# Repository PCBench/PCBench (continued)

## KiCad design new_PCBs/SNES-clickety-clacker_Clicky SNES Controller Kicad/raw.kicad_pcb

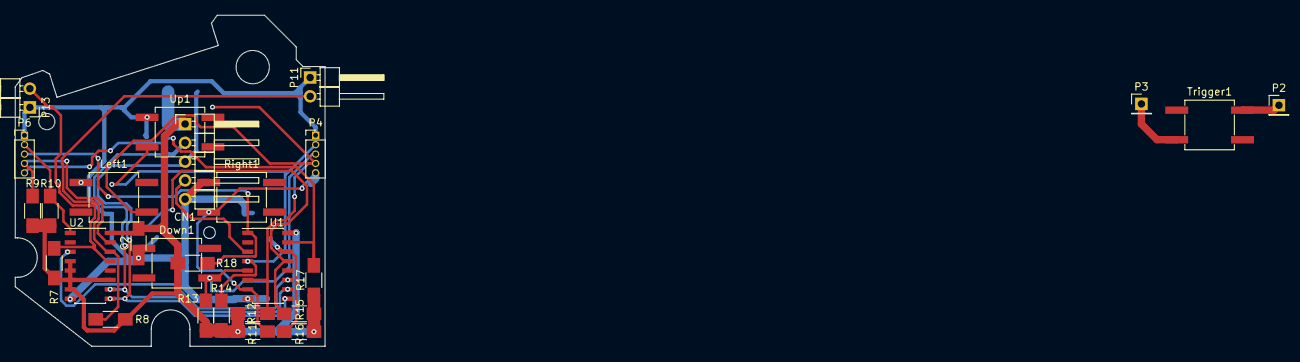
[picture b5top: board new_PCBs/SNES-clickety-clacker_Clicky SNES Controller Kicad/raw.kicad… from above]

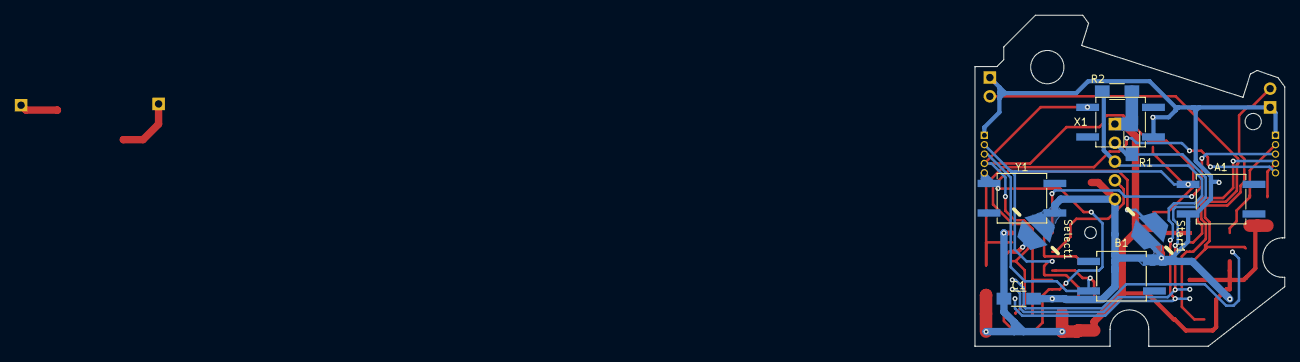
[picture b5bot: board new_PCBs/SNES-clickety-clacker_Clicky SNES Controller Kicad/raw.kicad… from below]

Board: 2 copper layers, 41.9 x 44.8 mm, 36 parts (9 on the bottom side), 20 nets.

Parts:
A1: SW_PUSH; SW_SPST_KSC7-G
B1: SW_PUSH; SW_SPST_KSC7-G
C1, C2: .1u; C_1206_HandSoldering
CN1: CN1; Pin_Header_Angled_1x05_Pitch2.54mm
Down1: SW_PUSH; SW_SPST_KSC2-G
Left1: SW_PUSH; SW_SPST_KSC2-G
P2: VSS_Trigger; Pin_Header_Straight_1x01_Pitch2.54mm
P3: TR_TL_OUT; Pin_Header_Straight_1x01_Pitch2.54mm
P4: DPAD_IN; Pin_Header_Straight_1x05_Pitch1.27mm
P6: ABXY_IN; Pin_Header_Straight_1x05_Pitch1.27mm
P11: TL_IN; Pin_Header_Angled_1x02_Pitch2.54mm
P13: TR_IN; Pin_Header_Angled_1x02_Pitch2.54mm
R1, R2, R7, R8, R9, R10, R11, R12, R13, R14, R15, R16, R17, R18: 47k; R_1206_HandSoldering
Right1: SW_PUSH; SW_SPST_KSC2-G
Select1: SW_PUSH; SW_SPST_Plated_Pad_5.5mm
Start1: SW_PUSH; SW_SPST_Plated_Pad_5.5mm
Trigger1: SW_PUSH; SW_SPST_KSC6-G
U1, U2: 4021; SOIC-16_3.9x9.9mm_Pitch1.27mm
Up1: SW_PUSH; SW_SPST_KSC2-G
X1: SW_PUSH; SW_SPST_KSC7-G
Y1: SW_PUSH; SW_SPST_KSC7-G

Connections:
+5V: C1.1, C2.1, CN1.1, R1.2, R2.2, R7.2, R8.2, R9.2, R10.2, R11.2, R12.2, R13.2, R14.2, R15.2, R16.2, R17.2, R18.2, U1.16, U2.4, U2.5, U2.6, U2.7, U2.11, U2.16
/A: P6.2, R10.1, U2.1
/A_switch: A1.2, P4.2, R14.1, U1.4, Up1.2
/B: P6.3, R18.1, U1.1
/B_switch: B1.2, Down1.2, P4.3, R13.1, U1.5
/DCLK: CN1.2, R1.1, U1.10, U2.10
/DLATCH: CN1.3, R2.1, U1.9, U2.9
/Left: Left1.2, P4.4, R12.1, U1.6, X1.2
/Right: P4.5, R11.1, Right1.2, U1.7, Y1.2
/SEROUT: CN1.4, U1.3
/Select: R16.1, Select1.2, U1.14
/Start: R15.1, Start1.2, U1.13
/TL: P11.2, R8.1, U2.14
/TR: P13.2, R7.1, U2.13
/VSS_Trigger: P2.1, Trigger1.1
/X: P6.4, R9.1, U2.15
/Y: P6.5, R17.1, U1.15
GND: A1.1, B1.1, C1.2, C2.2, CN1.5, Down1.1, Left1.1, P4.1, P6.1, P11.1, P13.1, Right1.1, Select1.1, Start1.1, U1.8, U2.8, Up1.1, X1.1, Y1.1
unnamed: P3.1, Trigger1.2
unnamed: U1.11, U2.3

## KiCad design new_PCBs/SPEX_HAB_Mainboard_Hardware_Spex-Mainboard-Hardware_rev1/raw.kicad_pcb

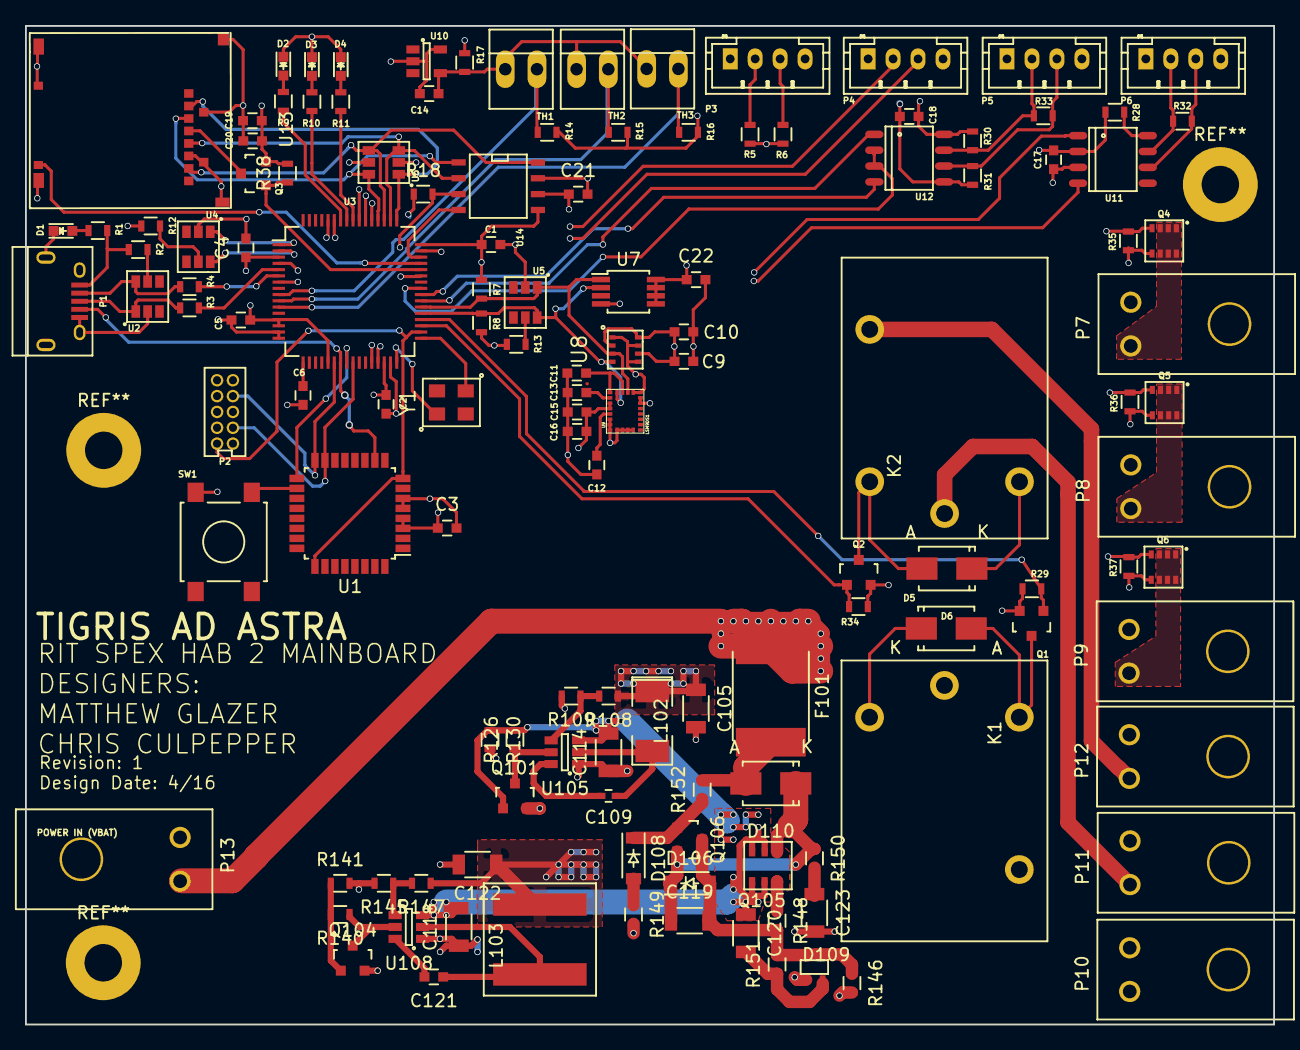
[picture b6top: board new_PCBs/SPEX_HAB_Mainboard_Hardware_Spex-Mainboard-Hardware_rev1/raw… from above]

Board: 4 copper layers, 100.0 x 80.0 mm, 131 parts (0 on the bottom side), 89 nets.

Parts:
C1, C2, C3, C4: 1uF; C_0603
C5: 2.2uF; C_0603
C6, C19: .1uF; C_0603
C9, C10, C17, C18, C21, C22: C; C_0603
C11, C13, C15: 100nF; C_0603
C12: 10nF; C_0603
C14: 4.7uF; C_0603
C16, C20: 10uF; C_0603
C105, C122: 47uf; C_1206
C109: 100nf; C_0402
C114, C118: 22uf; C_1206
C119, C123: 1uf 100v; C_1206
C120: .1uf 100v; C_1206
C121: 100nf; C_0603
D1, D2, D3, D4: LED; LED_0603
D5, D6: FM5819-W; SMA_Standard
D106, D108: ZENER; SOD-123
D109: D_Schottky_x2_Serial_AKC; sc70
D110: DIODE; Diode-SMA_Standard
F101: FUSE; Fuse_SMD2920
K1, K2: G5LE_1A4_DC3; G5LE-1A4-DC3
L102: 2.2uh; SMD-2010_Pol
L103: 3.3uh; NRS8030T3R3MJGJ
P1: USB_OTG; USB_Micro-B
P2: SWD Header; SWD-10
P3, P4, P5, P6: CONN_01X04; JST_PH_B4B-PH-K_04x2.00mm_Straight
P7, P8, P9, P10, P11, P12, P13: CONN_01X02; ultraFitCONN_2
Q1, Q2: 2N7002K; SOT-23
Q3: BSS215PH6327; SOT-23
Q4, Q5, Q6: Si5468DC; ChipFet-8
Q101, Q104: MOS_N_numbered; SOT-23
Q105: Si3407DV
Q106: Q_PNP_BEC; SOT-23
R1, R9, R10, R11: 1K; R_0603
R2, R12, R18, R29, R34, R38, R126, R130, R140, R141: 10K; R_0603
R3, R4: 33; R_0603
R5, R6, R7, R8: 4.7K; R_0603
R13, R30, R31, R35, R36, R37, R109, R145: 10k; R_0603
R14, R15, R16: 12k; R_0603
R17, R28: R; R_0603
R32, R33: 120; R_0603
R108, R146: 33.2k; R_0603
R147: 56.2k; R_0603
R148, R150: 10; R_0603
R149: 27.4k; R_0603
R151: 10.2k; R_0603
R152: 100k; R_0603
SW1: SW_PUSH; SW_SPST_B3S-1000
TH1, TH2, TH3: THERMISTOR; PINHEAD1-2
U1: MKL04Z32VLC4; LQFP-32_7x7mm_Pitch0.8mm
U2, U4, U5: NUP2201MR6; TSOP-6
U3: MK20DX256VLH7; LQFP-64_10x10mm_Pitch0.5mm
U6: MMQA6V2T1G; TSOP-6
U7: MCP9808T; MSOP-8_3x3mm_Pitch0.65mm
U8: BME280; LGA-8
U9: LSM9DS1; LGA-24
U10: LM4030; SOT-23-5
U11: MCP2551-I/SN; SO-8
U12: ST1480ABDR; SO-8
U13: SCHA4B0419; SCH4B0419
U14: AT45DB641E; SOIC-8-N
U105, U108: TPS563200; SOT-23-6
Y1: Crystal; CX3225GB16000D0HPQCC

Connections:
3.3V_MOS_CTRL: Q4.4, R35.2, U3.55
5V_MOS_CTRL: Q5.4, R36.2, U3.54
+3V3: C1.1, C2.1, C3.1, C4.1, C5.1, C9.1, C10.1, C11.1, C15.1, C16.1, C17.1, C18.1, C19.1, C20.1, C21.1, C22.1, C105.1, D5.1, D6.1, K1.4, K2.4, L102.1, P2.1, P3.1, P4.1, P5.1, P6.1, P7.2, Q3.2, R5.2, R6.2, R7.2, R8.2, R12.1, R13.1, R17.1, R18.1, R30.1, R38.2, R108.1, U1.3, U1.4, U3.3, U3.7, U3.13, U3.14, U3.21, U3.30, U3.48, U7.5, U7.6, U7.7, U7.8, U8.2, U8.6, U8.8, U9.1, U9.3, U9.7, U9.8, U9.22, U9.23, U11.3, U12.8, U14.5, U14.6
+5V: C122.1, L103.1, P8.2, R147.1
/Data_Input_Output/3.3V_MOS_OUT: P7.1, Q4.1, Q4.2, Q4.3, Q4.6, Q4.7, Q4.8
/Data_Input_Output/5V_MOS_OUT: P8.1, Q5.1, Q5.2, Q5.3, Q5.6, Q5.7, Q5.8
/Data_Input_Output/Battery_Out: K1.3, P10.1
/Data_Input_Output/CANH_out: P6.2, R32.1, U11.7
/Data_Input_Output/CANL_out: P6.3, R32.2, U11.6
/Data_Input_Output/RS485_A: P5.3, R31.1, R33.2, U12.6
/Data_Input_Output/RS485_B: P5.2, R30.2, R33.1, U12.7
/Data_Input_Output/User_In: K2.1, P11.1
/Data_Input_Output/User_Out: K2.3, P12.1
/Data_Input_Output/Vbus_MOS_OUT: P9.1, Q6.1, Q6.2, Q6.3, Q6.6, Q6.7, Q6.8
/HAB Sensors/2.5VRefVoltage: C14.1, R17.2, TH1.1, TH2.1, TH3.1, U10.4
/PTA6: P1.4, U1.10, U3.23
/PTA7: P2.2, U1.15, U3.25
/PTB0: P2.4, U1.16, U3.22
/PTB1: U1.17, U3.24
/PTB2: SW1.1, U1.18
CAN0_RX: U3.29, U11.4
CAN0_TX: U3.28, U11.1
Flash_Reset: R18.2, U3.43, U14.3
GND: C1.2, C2.2, C3.2, C4.2, C5.2, C6.2, C9.2, C10.2, C11.2, C12.2, C13.2, C14.2, C15.2, C16.2, C17.2, C18.2, C19.2, C20.2, C21.2, C22.2, C105.2, C114.1, C118.1, C122.2, C123.2, D1.1, D2.1, D3.1, D4.1, D109.1, P1.5, P1.6, P2.3, P2.5, P3.4, P4.4, P5.4, P6.4, P10.2, P11.2, P12.2, P13.1, Q1.2, Q2.2, Q4.5, Q5.5, Q6.5, Q101.2, Q104.2, R14.2, R15.2, R16.2, R28.2, R29.2, R31.2, R34.2, R35.1, R36.1, R37.1, R109.2, R130.2, R141.2, R145.2, R146.2, R149.2, SW1.2, U1.5, U1.6, U2.2, U3.4, U3.15, U3.16, U3.31, U3.47, U4.2, U5.2, U6.2, U6.5, U7.4, U8.1, U8.5, U8.7, U9.5, U9.6, U9.14, U9.15, U9.16, U9.17, U9.18, U9.19, U9.20, U10.2, U10.5, U11.2, U12.5, U13.6, U13.10, U14.7, U105.1, U108.1
I2C0_SCL: R8.1, U3.37, U5.6, U7.2, U8.4, U9.2
I2C0_SDA: R7.1, U3.38, U5.1, U7.1, U8.3, U9.4
I2C1_SCL: P3.3, R6.1, U3.2, U4.6
I2C1_SDA: P3.2, R5.1, U3.1, U4.1
LED_Heartbeat: R9.1, U3.58
LED_Status_1: R10.1, U3.57
LED_Status_2: R11.1, U3.56
unnamed: C6.1, U3.17
unnamed: C12.1, U9.21
unnamed: C13.1, U9.24
unnamed: C109.1, L102.2, U105.2
unnamed: C109.2, U105.6
unnamed: C119.1, D106.1, D110.1, Q105.4, Q106.2, R150.1
unnamed: C119.2, D106.2, D109.3, Q106.3, R146.1, R148.2, R151.2
unnamed: C120.2, D109.2, R151.1
unnamed: C121.1, L103.2, U108.2
unnamed: C121.2, U108.6
unnamed: C123.1, R150.2
unnamed: D1.2, R1.2
unnamed: D2.2, R9.2
unnamed: D3.2, R10.2
unnamed: D4.2, R11.2
unnamed: D5.2, K1.2, Q1.3
unnamed: D6.2, K2.2, Q2.3
unnamed: D108.1, Q106.1, R152.1
unnamed: D108.2, R149.1
unnamed: D110.2, F101.2, R152.2
unnamed: P1.1, R1.1, R2.2
unnamed: P1.2, R4.2, U2.6
unnamed: P1.3, R3.2, U2.1
unnamed: Q3.3, U13.4
unnamed: Q101.3, R126.1, U105.5
unnamed: Q104.3, R140.1, U108.5
unnamed: Q105.3, R148.1
unnamed: R2.1, U2.5
unnamed: R3.1, U3.5
unnamed: R4.1, U3.6
unnamed: R12.2, U4.5
unnamed: R13.2, U5.5
unnamed: R28.1, U11.8
unnamed: R108.2, R109.1, U105.4
unnamed: R145.1, R147.2, U108.4
unnamed: U3.32, Y1.1
unnamed: U3.33, Y1.2
RESET_b: P2.10, U1.8, U1.25, U3.34
RX/TX_CTRL: U3.41, U12.2, U12.3
Relay1_ctrl: Q1.1, R29.1, U3.36
Relay2_ctrl: Q2.1, R34.1, U3.35
SD_CTRL: Q3.1, R38.1, U3.44
SD_Detect: U3.45, U13.9
SPI0_CS0: U3.49, U6.1, U13.2
SPI0_CS1: U3.46, U14.4
SPI0_MISO: U3.51, U6.4, U13.7, U14.8
SPI0_MOSI: U3.52, U6.6, U13.3, U14.1
SPI0_SCK: U3.50, U6.3, U13.5, U14.2
Temp1: R14.1, TH1.2, U3.9
Temp2: R15.1, TH2.2, U3.10
Temp3: R16.1, TH3.2, U3.11
UART0_RX: U3.39, U12.1
UART0_TX: U3.40, U12.4
UART2_RX: P4.3, U3.59
UART2_TX: P4.2, U3.60
VBatt: F101.1, K1.1, P13.2
Vbus: C114.2, C118.2, C120.1, P9.2, Q101.1, Q104.1, Q105.1, Q105.2, Q105.5, Q105.6, R126.2, R130.1, R140.2, R141.1, U105.3, U108.3
Vbus_MOS_CTRL: Q6.4, R37.2, U3.53

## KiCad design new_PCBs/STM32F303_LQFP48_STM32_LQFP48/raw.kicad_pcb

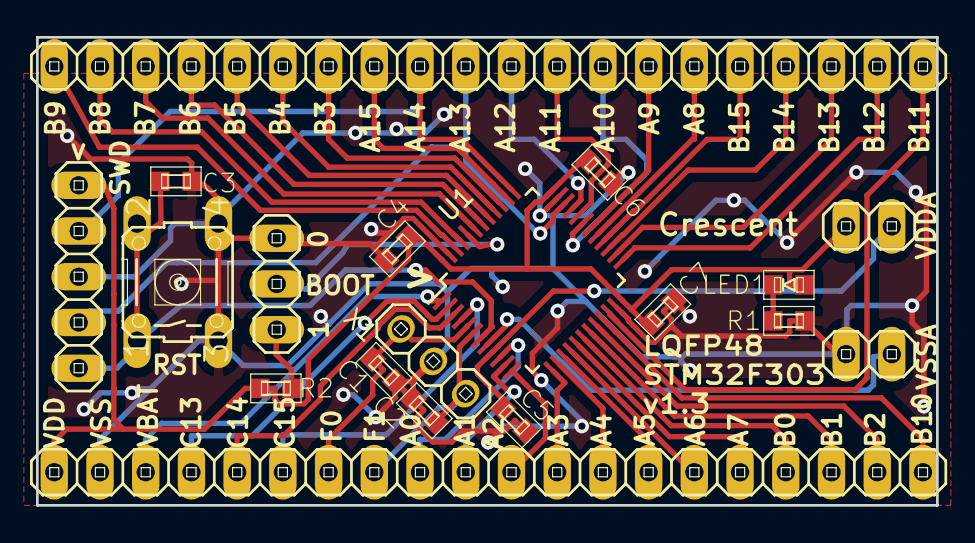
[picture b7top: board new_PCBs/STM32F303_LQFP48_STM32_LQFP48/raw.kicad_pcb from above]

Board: 2 copper layers, 50.0 x 26.0 mm, 19 parts (0 on the bottom side), 46 nets.

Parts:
C1, C2, C3, C4, C5, C6, C7: CAPACITOR1608; generic-SMD1608
JP1: PINHD-1X5; pinhead-1X05
JP2: PINHD-1X3; pinhead-1X03
JP3, JP5: PINHD-1X2; pinhead-1X02
JP4, JP6: PINHD-1X20; pinhead-1X20
LED1: LED1608; generic-LED1608
R1, R2: RESISTOR1608; generic-SMD1608
S1: 10-XX; switch-omron-B3F-10XX
U1: STM32F100C8; LQFP-48_7x7mm_Pitch0.5mm
X1: CRYSTAL_SMD; pinhead-1X03

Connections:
BOOT: JP2.2, U1.44
NRST: C3.1, JP1.5, S1.1, S1.2, U1.7
unnamed: JP2.1, R2.2
unnamed: LED1.K, R1.1
OSCI: C1.1, JP4.7, U1.5, X1.1
OSCO: C2.1, JP4.8, U1.6, X1.2
PA0: JP4.9, U1.10
PA1: JP4.10, U1.11
PA2: JP4.11, U1.12
PA3: JP4.12, U1.13
PA4: JP4.13, U1.14
PA5: JP4.14, U1.15
PA6: JP4.15, U1.16
PA7: JP4.16, U1.17
PA8: JP6.15, U1.29
PA9: JP6.14, U1.30
PA10: JP6.13, U1.31
PA11: JP6.12, U1.32
PA12: JP6.11, U1.33
PA13: JP1.4, JP6.10, U1.34
PA14: JP1.2, JP6.9, U1.37
PA15: JP6.8, U1.38
PB0: JP4.17, U1.18
PB1: JP4.18, U1.19
PB2: JP4.19, U1.20
PB3: JP6.7, U1.39
PB4: JP6.6, U1.40
PB5: JP6.5, U1.41
PB6: JP6.4, U1.42
PB7: JP6.3, U1.43
PB8: JP6.2, U1.45
PB9: JP6.1, U1.46
PB10: JP4.20, U1.21
PB11: JP6.20, U1.22
PB12: JP6.19, U1.25
PB13: JP6.18, U1.26
PB14: JP6.17, U1.27
PB15: JP6.16, U1.28
PC13: JP4.4, U1.2
PC14: JP4.5, U1.3
PC15: JP4.6, U1.4
VBAT: JP4.3, U1.1
VDD: C4.1, C6.1, C7.1, JP1.1, JP3.1, JP4.1, LED1.A, R2.1, U1.24, U1.36, U1.48
VDDA: C5.1, JP3.2, U1.9
VSS: C1.2, C2.2, C3.2, C4.2, C5.2, C6.2, C7.2, JP1.3, JP2.3, JP4.2, JP5.1, R1.2, S1.3, S1.4, U1.23, U1.35, U1.47, X1.3
VSSA: JP5.2, U1.8
